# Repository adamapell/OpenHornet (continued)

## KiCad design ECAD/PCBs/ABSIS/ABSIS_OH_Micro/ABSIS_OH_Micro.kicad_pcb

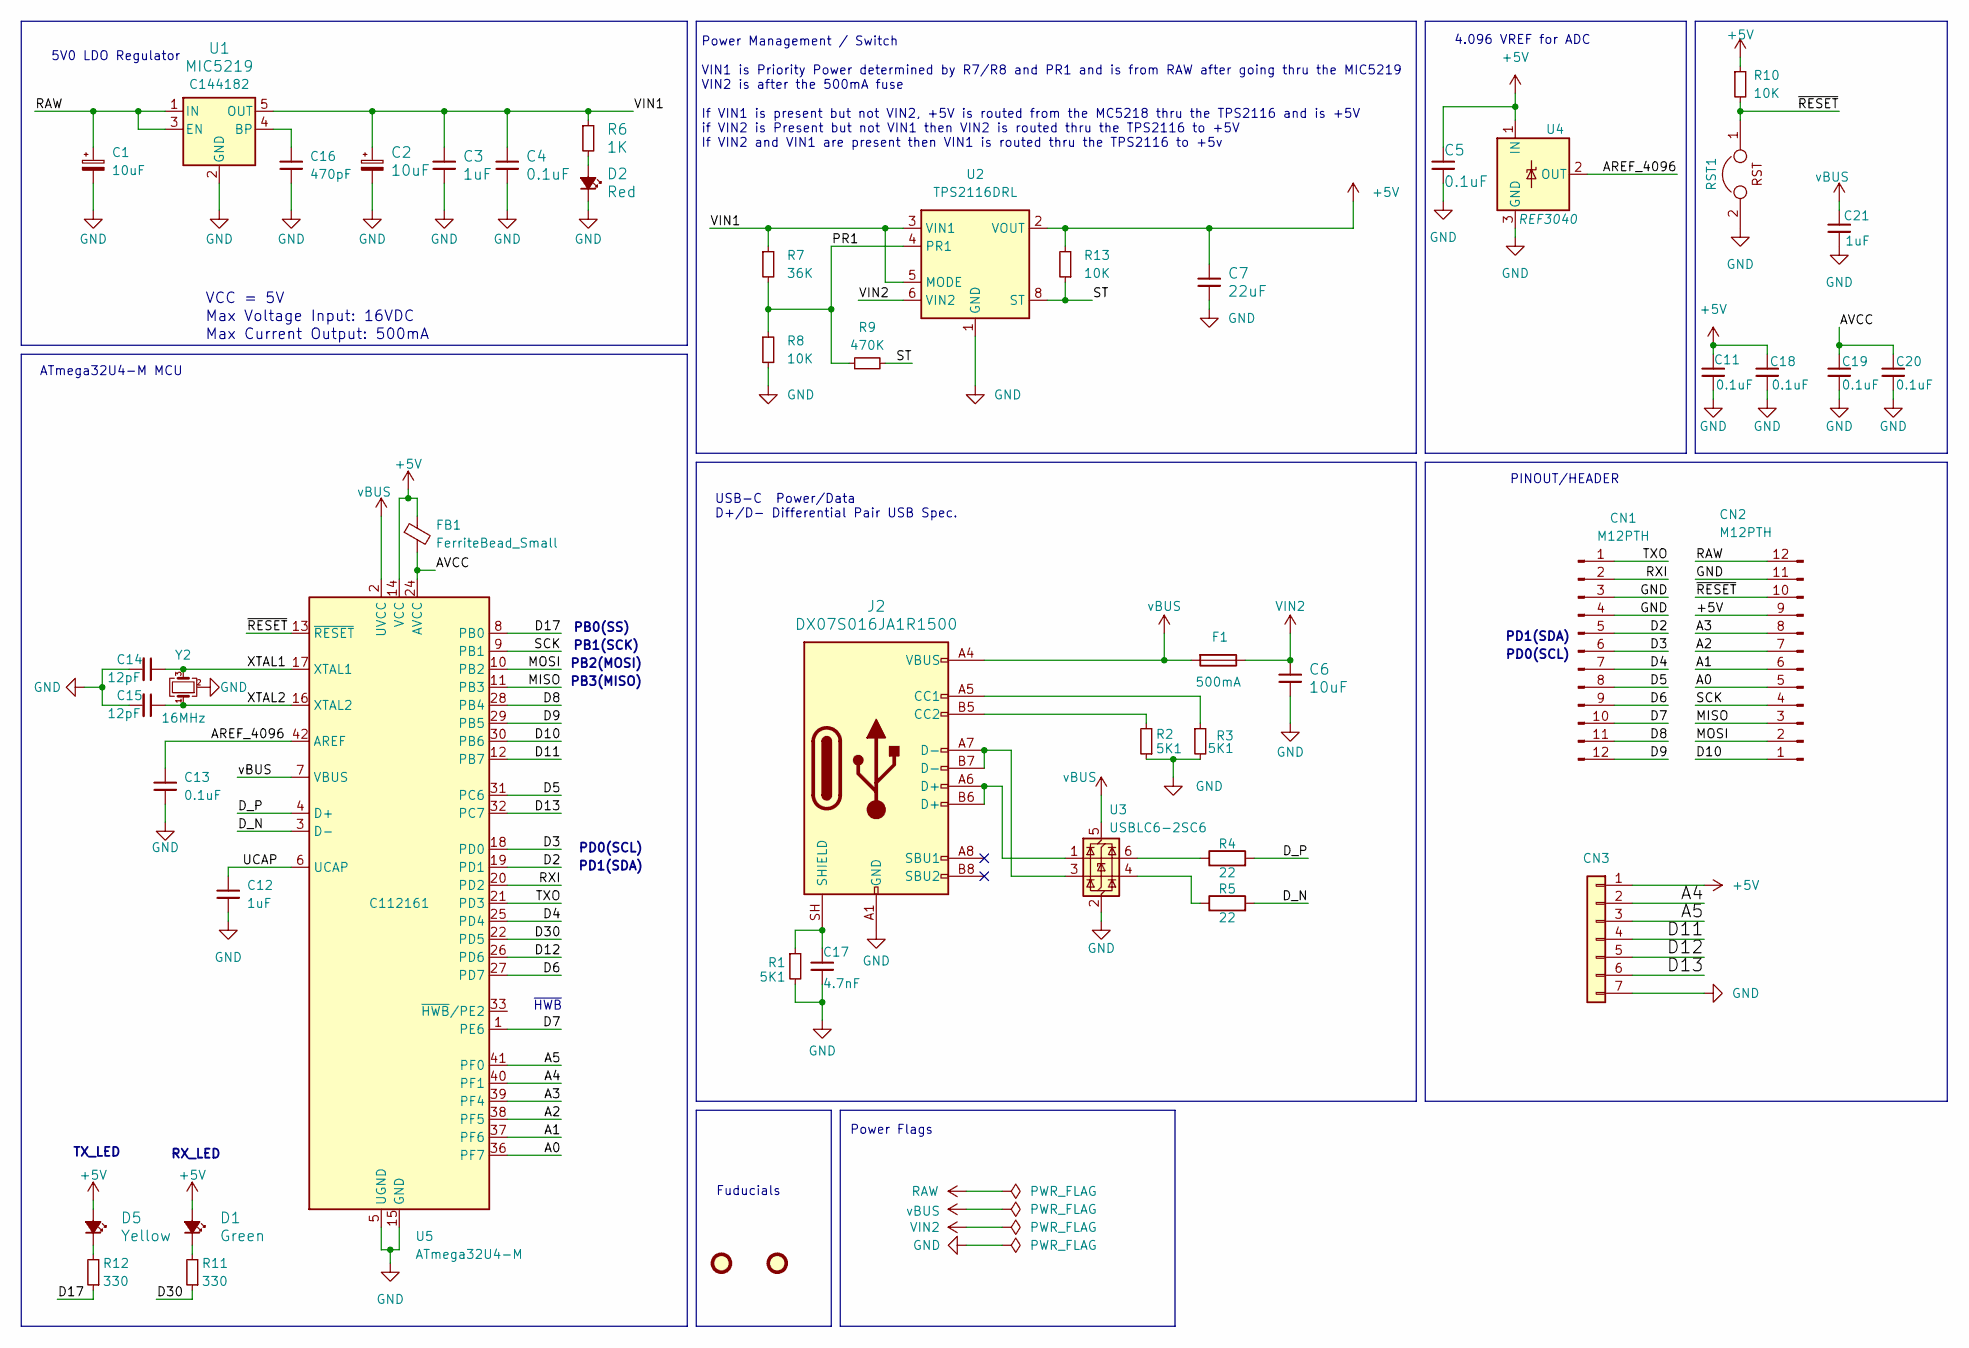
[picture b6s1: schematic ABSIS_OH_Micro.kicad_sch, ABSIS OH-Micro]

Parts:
C1: 10uF; CP_EIA-3216-18_Kemet-A; LCSC C110055
C2: 10uF; CP_EIA-3216-18_Kemet-A; LCSC Part C110055
C3, C12, C21: 1uF; C_0402_1005Metric; LCSC C1592
C4, C5, C13: 0.1uF; C_0402_1005Metric; LCSC C696360
C6: 10uF; C_0402_1005Metric; LCSC C696360
C7: 22uF; C_0805_2012Metric; LCSC C696360
C11, C18, C19, C20: 0.1uF; C_0402_1005Metric; LCSC C1592
C14, C15: 12pF; C_0402_1005Metric; LCSC C599692
C16: 470pF; C_0402_1005Metric; LCSC C184771
C17: 4.7nF; C_0402_1005Metric; LCSC C1592
CN1, CN2: M12PTH; PinHeader_1x12_P2.54mm_Vertical; LCSC C2840012
CN3: PinHeader_1x06_P2.00mm_Vertical; LCSC C37208
D1: Green; LED_0402_1005Metric; LCSC C74338
D2: Red; LED_0603_1608Metric; LCSC C84263
D5: Yellow; LED_0402_1005Metric; LCSC C434450
F1: 500mA; Fuse_1206_3216Metric; LCSC C136341
FB1: FerriteBead_Small; L_0402_1005Metric
J2: DX07S016JA1R1500; USB_C_Receptacle_JAE_DX07S016JA1R1500; LCSC# C3197885
JP3, JP6: FIDUCIALUFIDUCIAL; Fiducial_0.5mm_Mask1.5mm
R1, R2, R3: 5K1; R_0402_1005Metric; LCSC C844933
R4, R5: 22; R_0402_1005Metric; Manufacturer PN 0603WAF220JT5E; LCSC C23345
R6: 1K; R_0402_1005Metric; LCSC C22548
R7: 36K; R_0402_1005Metric; LCSC C114661
R8, R13: 10K; R_0402_1005Metric; LCSC C99782
R9: 470K; R_0402_1005Metric; LCSC C99782
R10: 10K; R_0402_1005Metric; LCSC C98220
R11, R12: 330; R_0402_1005Metric; LCSC C105881
RST1: RST; SolderJumper-2_P1.3mm_Open_RoundedPad1.0x1.5mm
U1: MIC5219; SOT-23-5; LCSC C144182
U2: TPS2116DRL; SOT-583-8; LCSC C3235557
U3: USBLC6-2SC6; SOT-23-6
U4: REF3040; SOT-23; LCSC C19415
U5: ATmega32U4-M; QFN-44-1EP_7x7mm_P0.5mm_EP5.2x5.2mm; LCSC C112161
Y2: 16MHz; Crystal_SMD_3225-4Pin_3.2x2.5mm; LCSC C13738

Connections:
+5V: C5.2, C7.2, C11.2, C18.2, CN2.9, CN3.1, D1.2 (A), D5.2 (A), FB1.1, R10.1, R13.2, U2.2 (VOUT), U2.7 (VOUT), U4.1 (IN), U5.14 (VCC), U5.34 (VCC)
/A0: CN2.5, U5.36 (PF7)
/A1: CN2.6, U5.37 (PF6)
/A2: CN2.7, U5.38 (PF5)
/A3: CN2.8, U5.39 (PF4)
/A4: CN3.2, U5.40 (PF1)
/A5: CN3.3, U5.41 (PF0)
/AREF_4096: C13.2, U4.2 (OUT), U5.42 (AREF)
/AVCC: C19.2, C20.2, FB1.2, U5.24 (AVCC), U5.44 (AVCC)
/D2: CN1.5, U5.19 (PD1)
/D3: CN1.6, U5.18 (PD0)
/D4: CN1.7, U5.25 (PD4)
/D5: CN1.8, U5.31 (PC6)
/D6: CN1.9, U5.27 (PD7)
/D7: CN1.10, U5.1 (PE6)
/D8: CN1.11, U5.28 (PB4)
/D9: CN1.12, U5.29 (PB5)
/D10: CN2.1, U5.30 (PB6)
/D11: CN3.4, U5.12 (PB7)
/D12: CN3.5, U5.26 (PD6)
/D13: CN3.6, U5.32 (PC7)
/D17: R12.1, U5.8 (PB0)
/D30: R11.1, U5.22 (PD5)
/D_N: R5.2, U5.3 (D-)
/D_P: R4.2, U5.4 (D+)
/MISO: CN2.3, U5.11 (PB3)
/MOSI: CN2.2, U5.10 (PB2)
/PR1: R7.2, R8.1, R9.1, U2.4 (PR1)
/RXI: CN1.2, U5.20 (PD2)
/SCK: CN2.4, U5.9 (PB1)
/ST: R9.2, R13.1, U2.8 (ST)
/TXO: CN1.1, U5.21 (PD3)
/UCAP: C12.2, U5.6 (UCAP)
/VIN1: C2.1, C3.1, C4.2, R6.1, R7.1, U1.5 (OUT), U2.3 (VIN1), U2.5 (MODE)
/XTAL1: C14.1, U5.17 (XTAL1), Y2.3
/XTAL2: C15.1, U5.16 (XTAL2), Y2.1
/~RESET: CN2.10, R10.2, RST1.1, U5.13 (~RESET)
GND: C1.2, C2.2, C3.2, C4.1, C5.1, C6.1, C7.1, C11.1, C12.1, C13.1, C14.2, C15.2, C16.2, C17.1, C18.1, C19.1, C20.1, C21.1, CN1.3, CN1.4, CN2.11, CN3.7, D2.1 (K), J2.A1 (GND), J2.A12 (GND), J2.B1 (GND), J2.B12 (GND), R1.2, R2.1, R3.2, R8.2, RST1.2, U1.2 (GND), U2.1 (GND), U3.2 (GND), U4.3 (GND), U5.5 (UGND), U5.15 (GND), U5.23 (GND), U5.35 (GND), U5.43 (GND), U5.45 (GND), Y2.2 (G), Y2.4 (G)
unnamed: D1.1 (K), R11.2
unnamed: D2.2 (A), R6.2
unnamed: D5.1 (K), R12.2
unnamed: J2.A5 (CC1), R3.1
unnamed: J2.B5 (CC2), R2.2
unnamed: J2.A6 (D+), J2.B6 (D+), U3.1 (I/O1)
unnamed: J2.A7 (D-), J2.B7 (D-), U3.3 (I/O2)
unnamed: C17.2, J2.SH (SHIELD), R1.1
unnamed: R4.1, U3.6 (I/O1)
unnamed: R5.1, U3.4 (I/O2)
unnamed: C16.1, U1.4 (BP)
RAW: C1.1, CN2.12, U1.1 (IN), U1.3 (EN)
VIN2: C6.2, F1.1, U2.6 (VIN2)
vBUS: C21.2, F1.2, J2.A4 (VBUS), J2.A9 (VBUS), J2.B4 (VBUS), J2.B9 (VBUS), U3.5 (VBUS), U5.2 (UVCC), U5.7 (VBUS)

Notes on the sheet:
PB0(SS)
RX_LED
5V0 LDO Regulator
PB2(MOSI)
PD0(SCL)
PB1(SCK)
USB-C Power/Data D+/D- Differential Pair USB Spec.
~{HWB}
4.096 VREF for ADC
Fuducials
PD1(SDA)
Max Voltage Input: 16VDC
TX_LED
Max Current Output: 500mA
ATmega32U4-M MCU
Power Flags
PB3(MISO)
PINOUT/HEADER
VCC = 5V
Power Management / Switch VIN1 is Priority Power determined by R7/R8 and PR1 and is from RAW after going thru the MIC5219 VIN2 is after the 500mA fuse If VIN1 is present but not VIN2, +5V is routed from the MC5218 thru the TPS2116 and is +5V if VIN2 is Present but not VIN1 then VIN2 is routed thru 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

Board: 4 copper layers, 50 parts (4 on the bottom side), 52 nets, no tracks yet.

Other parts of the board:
LOGO: LOGO; LOGO_OH_NoText_Small
